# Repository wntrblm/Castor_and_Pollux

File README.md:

# Winterbloom Castor & Pollux

Castor & Pollux is a Roland Juno-inspired oscillator in Eurorack format.

More details available at https://winterbloom.com/shop/winterbloom-castor-and-pollux

## Repository layout

This repository contains the hardware design files, firmware files, factory setup scripts, and user guide for Castor & Pollux.

- **factory/** contains the scripts used to program, test, and calibrate the module after assembly. These scripts are all written in Python.
- **firmware/** contains the firmware source code, build scripts, and third-party dependencies. The firmware is written in C using GCC ARM.
- **hardware/** contains the hardware design files for the mainboard, jackboard, panel, and programming board. These are all created using KiCAD.
- **user_guide/** contains the user's guide source files. These are written in Markdown and published using MkDocs.

## License and contributing

Castor & Pollux is open-source hardware and software, however, licensing a project like this is a little complicated. Please take a chance to review the [LICENSE](LICENSE.md) file.

We welcome contributions! Please read our [Contributing Guide](CONTRIBUTING.md) and [Code of Conduct](CODE_OF_CONDUCT.md).

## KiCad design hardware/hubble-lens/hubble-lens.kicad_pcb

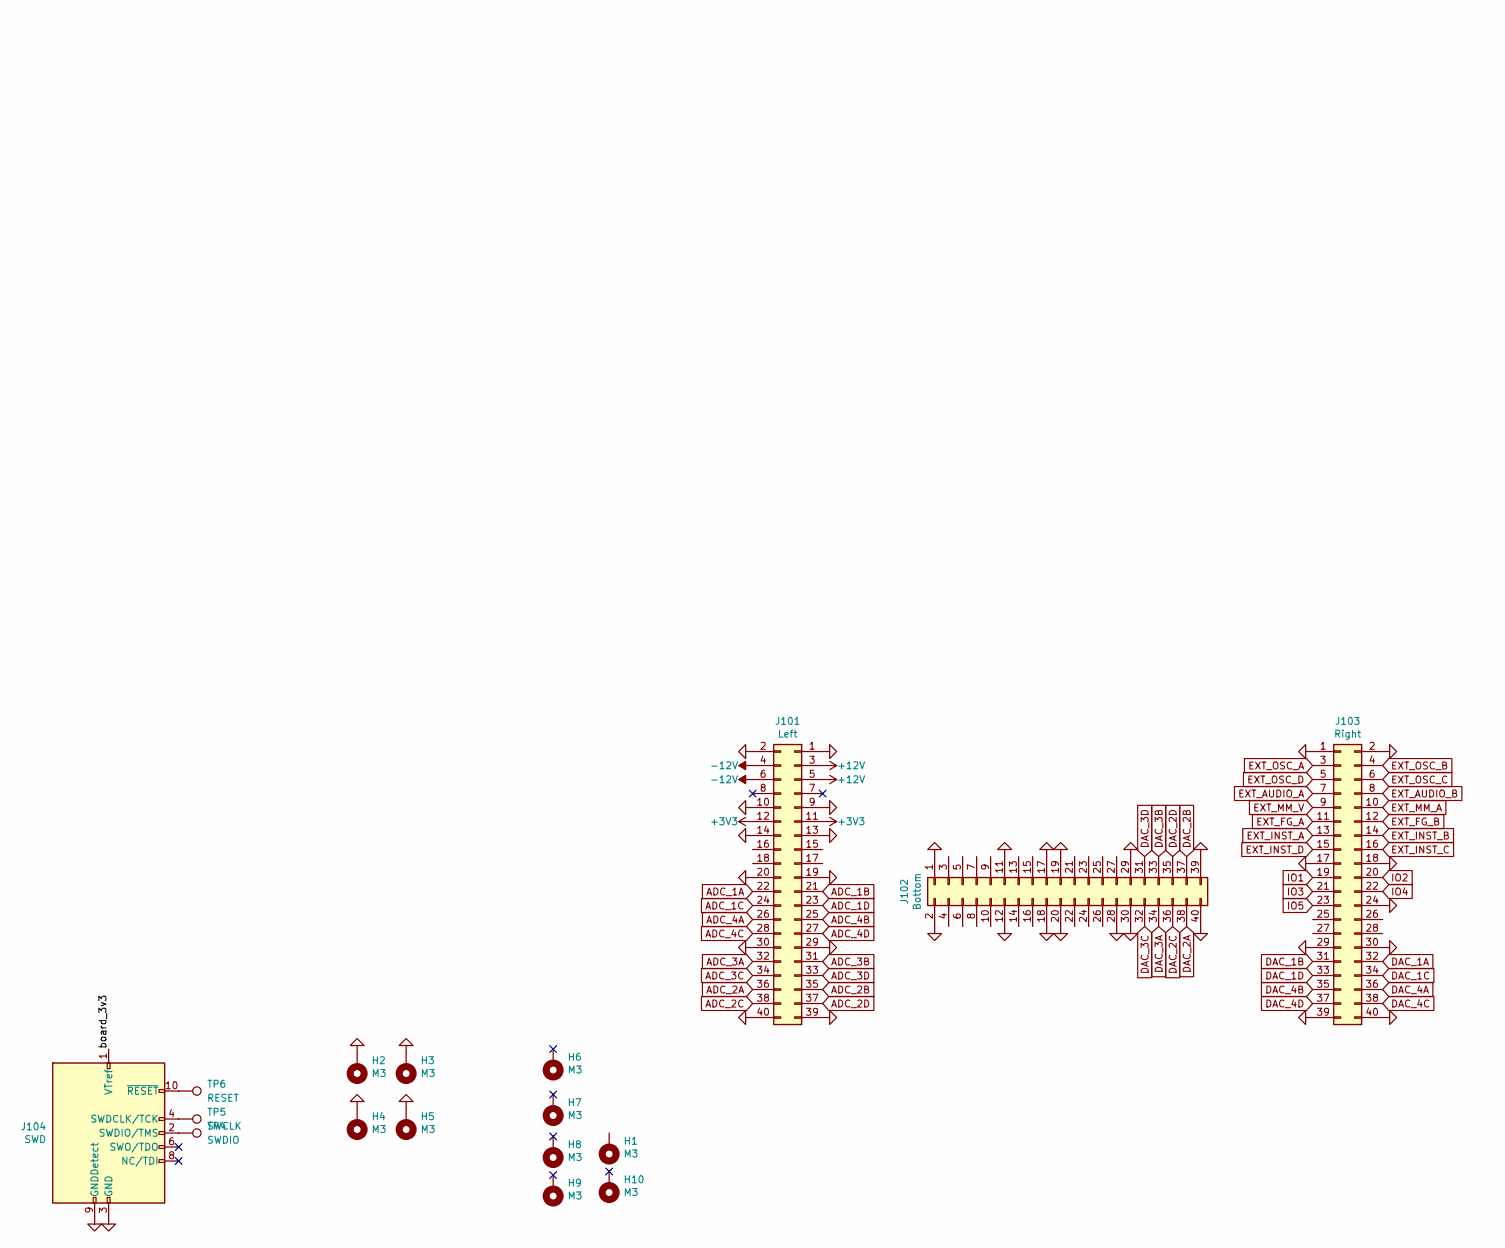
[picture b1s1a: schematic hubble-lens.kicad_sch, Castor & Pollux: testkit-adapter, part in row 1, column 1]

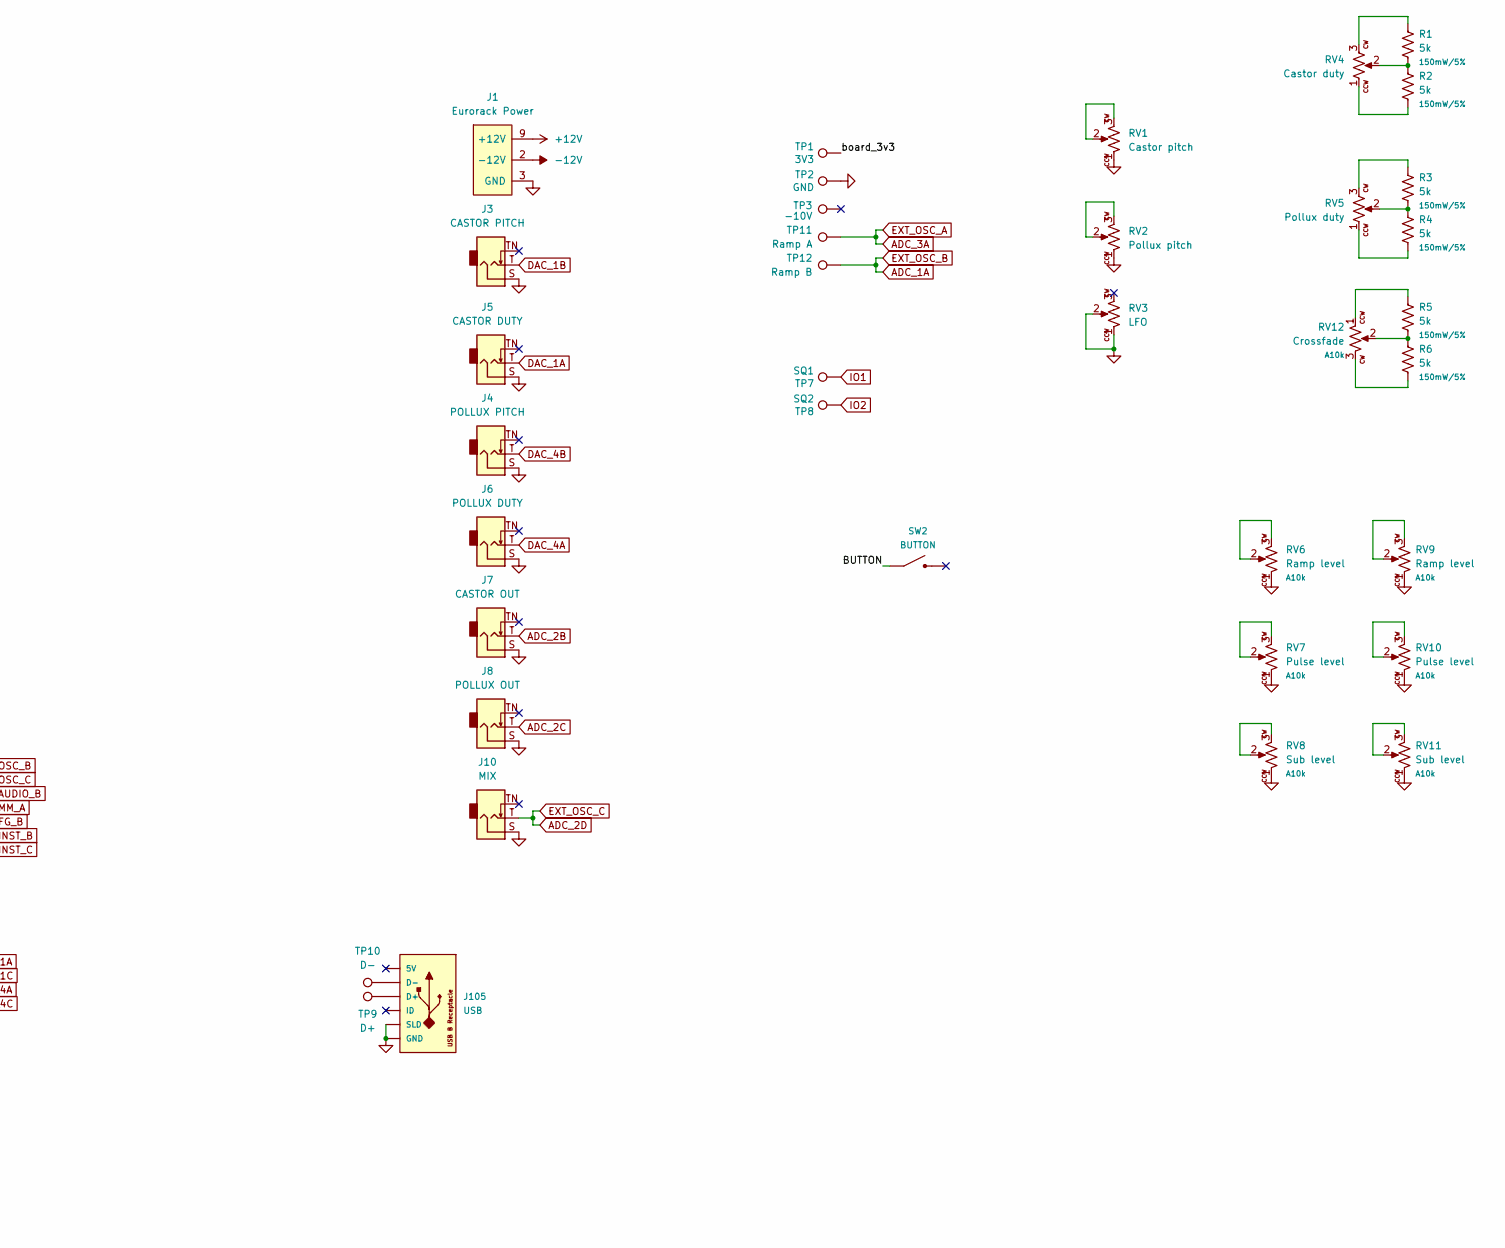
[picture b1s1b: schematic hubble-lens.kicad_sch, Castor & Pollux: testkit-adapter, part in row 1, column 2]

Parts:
H1, H6, H7, H8, H9, H10: M3; MountingHole_3.2mm_M3
H2, H3, H4, H5: M3; MountingHole_3.2mm_M3_Pad_Via
J1: Eurorack Power; Eurorack_Power_2x5_Shrouded; MPN 4UCONN 20253, On-shore 302-S101
J3: CASTOR PITCH; AudioJack_WQP518MA; MPN WQP-WQP518MA
J4: POLLUX PITCH; AudioJack_WQP518MA; MPN WQP-WQP518MA
J5: CASTOR DUTY; AudioJack_WQP518MA; MPN WQP-WQP518MA
J6: POLLUX DUTY; AudioJack_WQP518MA; MPN WQP-WQP518MA
J7: CASTOR OUT; AudioJack_WQP518MA; MPN WQP-WQP518MA
J8: POLLUX OUT; AudioJack_WQP518MA; MPN WQP-WQP518MA
J10: MIX; AudioJack_WQP518MA; MPN WQP-WQP518MA
J101: Left; PinSocket_2x20_P2.54mm_Vertical
J102: Bottom; PinSocket_2x20_P2.54mm_Vertical
J103: Right; PinSocket_2x20_P2.54mm_Vertical
J104: SWD; PinHeader_2x05_P1.27mm_Vertical
J105: USB; USB_B_Micro_Receptacle
R1, R2, R3, R4, R5, R6: 5k; R_0603_HandSolder; Rating 150mW/5%
RV1: Castor pitch; Potentiometer_Alpha_R0904N; Rating A10k
RV2: Pollux pitch; Potentiometer_Alpha_R0904N; Rating A10k
RV3: LFO; Potentiometer_Alpha_R0904N; Rating A10k
RV4: Castor duty; Potentiometer_Alpha_R0904N; Rating A10k
RV5: Pollux duty; Potentiometer_Alpha_R0904N; Rating A10k
RV6, RV9: Ramp level; Potentiometer_Alpha_R0904N; Rating A10k; MPN R0904N-B10K L-25KQ/LWS
RV7, RV10: Pulse level; Potentiometer_Alpha_R0904N; Rating A10k; MPN R0904N-B10K L-25KQ/LWS
RV8, RV11: Sub level; Potentiometer_Alpha_R0904N; Rating A10k; MPN R0904N-B10K L-25KQ/LWS
RV12: Crossfade; Potentiometer_Alpha_R0904N; Rating A10k
SW2: BUTTON; Tactile_Switch_6mm; MPN TL1105SPF160Q, TL1105SPF100Q, TL1105SPF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
TP1: 3V3; TestPoint_THTPad_D2.0mm_Drill1.0mm
TP2: GND; TestPoint_THTPad_D2.0mm_Drill1.0mm
TP3: -10V; TestPoint_THTPad_D2.0mm_Drill1.0mm
TP4: SWDIO; TestPoint_THTPad_D2.0mm_Drill1.0mm
TP5: SWCLK; TestPoint_THTPad_D2.0mm_Drill1.0mm
TP6: RESET; TestPoint_THTPad_D2.0mm_Drill1.0mm
TP7: SQ1; TestPoint_THTPad_D2.0mm_Drill1.0mm
TP8: SQ2; TestPoint_THTPad_D2.0mm_Drill1.0mm
TP9: D+; TestPoint_THTPad_D2.0mm_Drill1.0mm
TP10: D-; TestPoint_THTPad_D2.0mm_Drill1.0mm
TP11: Ramp A; TestPoint_THTPad_D2.0mm_Drill1.0mm
TP12: Ramp B; TestPoint_THTPad_D2.0mm_Drill1.0mm

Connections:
+3V3: J101.11, J101.12
+12V: J1.9 (+12V), J1.10 (+12V), J101.3, J101.5
-12V: J1.1 (-12V), J1.2 (-12V), J101.4, J101.6
/BUTTON: SW2.1
/board_3v3: J104.1 (VTref), TP1.1
ADC_1A: J101.22, J103.4, TP12.1
ADC_1B: J101.21
ADC_1C: J101.24
ADC_1D: J101.23
ADC_2A: J101.36
ADC_2B: J7.T (Tip), J101.35
ADC_2C: J8.T (Tip), J101.38
ADC_2D: J10.T (Tip), J101.37, J103.6
ADC_3A: J101.32, J103.3, TP11.1
ADC_3B: J101.31
ADC_3C: J101.34
ADC_3D: J101.33
ADC_4A: J101.26
ADC_4B: J101.25
ADC_4C: J101.28
ADC_4D: J101.27
DAC_1A: J5.T (Tip), J103.32
DAC_1B: J3.T (Tip), J103.31
DAC_1C: J103.34
DAC_1D: J103.33
DAC_2A: J102.38
DAC_2B: J102.37
DAC_2C: J102.36
DAC_2D: J102.35
DAC_3A: J102.34
DAC_3B: J102.33
DAC_3C: J102.32
DAC_3D: J102.31
DAC_4A: J6.T (Tip), J103.36
DAC_4B: J4.T (Tip), J103.35
DAC_4C: J103.38
DAC_4D: J103.37
EXT_AUDIO_A: J103.7
EXT_AUDIO_B: J103.8
EXT_FG_A: J103.11
EXT_FG_B: J103.12
EXT_INST_A: J103.13
EXT_INST_B: J103.14
EXT_INST_C: J103.16
EXT_INST_D: J103.15
EXT_MM_A: J103.10
EXT_MM_V: J103.9
EXT_OSC_D: J103.5
GND: H2.1, H3.1, H4.1, H5.1, J1.3 (GND), J1.4 (GND), J1.5 (GND), J1.6 (GND), J1.7 (GND), J1.8 (GND), J3.S (Sleeve), J4.S (Sleeve), J5.S (Sleeve), J6.S (Sleeve), J7.S (Sleeve), J8.S (Sleeve), J10.S (Sleeve), J101.1, J101.2, J101.9, J101.10, J101.13, J101.14, J101.19, J101.20, J101.29, J101.30, J101.39, J101.40, J102.1, J102.2, J102.11, J102.12, J102.17, J102.18, J102.19, J102.20, J102.28, J102.29, J102.30, J102.39, J102.40, J103.1, J103.2, J103.17, J103.18, J103.24, J103.29, J103.30, J103.39, J103.40, J104.3 (GND), J104.5 (GND), J104.9 (GNDDetect), J105.5 (GND), J105.S1 (SLD), J105.S2 (SLD), J105.S3 (SLD), J105.S4 (SLD), J105.S5 (SLD), J105.S6 (SLD), RV1.1, RV2.1, RV3.1, RV3.2, RV6.1, RV7.1, RV8.1, RV9.1, RV10.1, RV11.1, TP2.1
IO1: J103.19, TP7.1
IO2: J103.20, TP8.1
IO3: J103.21
IO4: J103.22
IO5: J103.23
unnamed: J104.2 (SWDIO/TMS), TP4.1
unnamed: J104.4 (SWDCLK/TCK), TP5.1
unnamed: J104.10 (~RESET), TP6.1
unnamed: RV1.2, RV1.3
unnamed: RV2.2, RV2.3
unnamed: R2.1, RV4.1
unnamed: R1.1, R2.2, RV4.2
unnamed: R1.2, RV4.3
unnamed: R4.1, RV5.1
unnamed: R3.1, R4.2, RV5.2
unnamed: R3.2, RV5.3
unnamed: RV6.2, RV6.3
unnamed: RV7.2, RV7.3
unnamed: RV8.2, RV8.3
unnamed: RV9.2, RV9.3
unnamed: RV10.2, RV10.3
unnamed: RV11.2, RV11.3
unnamed: R5.2, RV12.1
unnamed: R5.1, R6.2, RV12.2
unnamed: R6.1, RV12.3
unnamed: J105.3 (D+), TP9.1
unnamed: J105.2 (D-), TP10.1

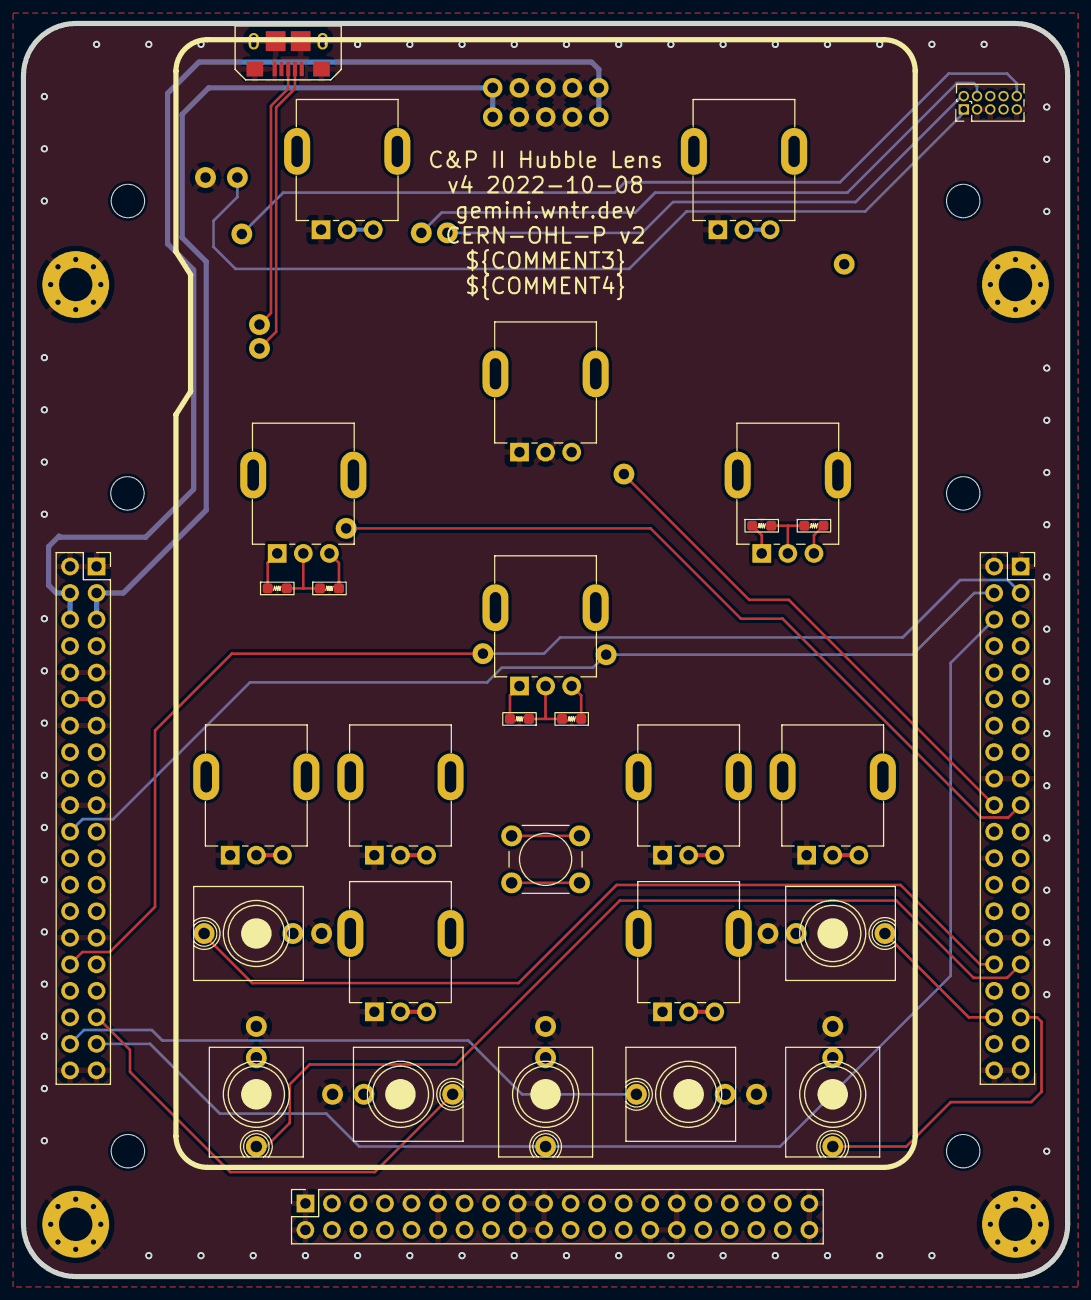
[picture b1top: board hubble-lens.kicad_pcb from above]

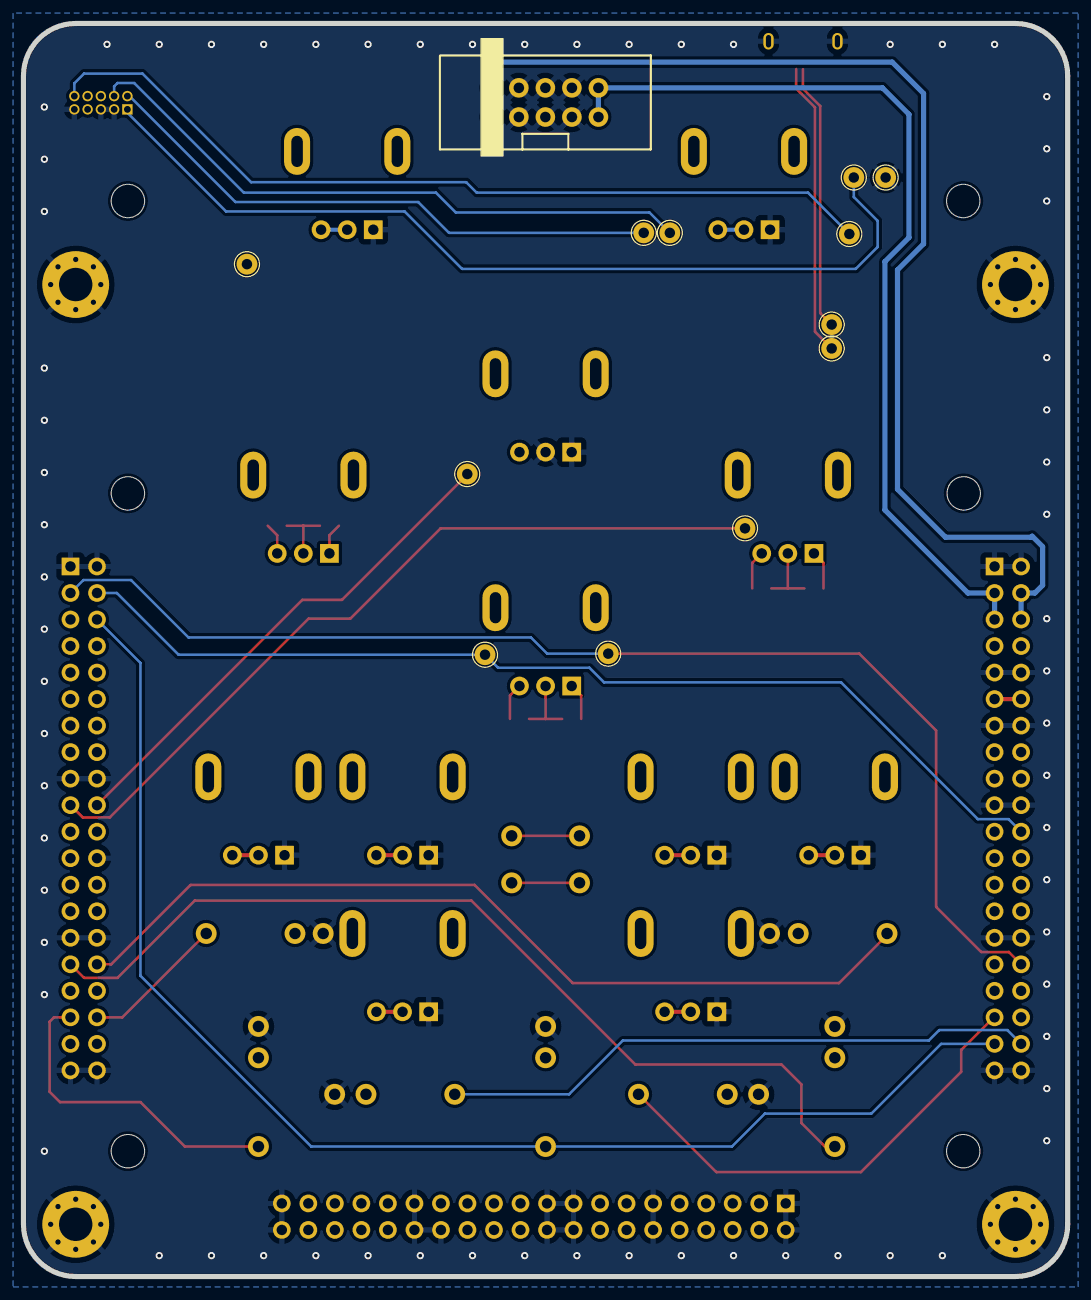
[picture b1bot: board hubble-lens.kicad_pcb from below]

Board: 2 copper layers, 100.0 x 120.0 mm, 54 parts (13 on the bottom side), 38 nets.

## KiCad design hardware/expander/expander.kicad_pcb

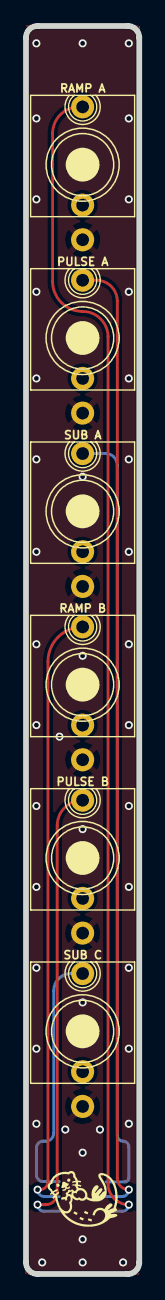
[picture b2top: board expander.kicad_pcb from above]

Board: 2 copper layers, 9.8 x 108.0 mm, 7 parts (1 on the bottom side), 7 nets.

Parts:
J1: EXT; Connector_Cortex_Debug_IDC_2x05_P1.27mm_Vertical_Shrouded_S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
J2: RAMP A; AudioJack_WQP518MA
J3: PULSE A; AudioJack_WQP518MA
J4: SUB A; AudioJack_WQP518MA
J5: RAMP B; AudioJack_WQP518MA
J6: PULSE B; AudioJack_WQP518MA
J7: SUB C; AudioJack_WQP518MA

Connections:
/CASTOR_PULSE_IN: J1.6, J3.T (Tip)
/CASTOR_RAMP_IN: J1.4, J2.T (Tip)
/CASTOR_SUB_IN: J1.8, J4.T (Tip)
/POLLUX_PULSE_IN: J1.3, J6.T (Tip)
/POLLUX_RAMP_IN: J1.5, J5.T (Tip)
/POLLUX_SUB_IN: J1.7, J7.T (Tip)
GND: J1.1, J1.2, J1.9, J1.10, J2.S (Sleeve), J3.S (Sleeve), J4.S (Sleeve), J5.S (Sleeve), J6.S (Sleeve), J7.S (Sleeve)

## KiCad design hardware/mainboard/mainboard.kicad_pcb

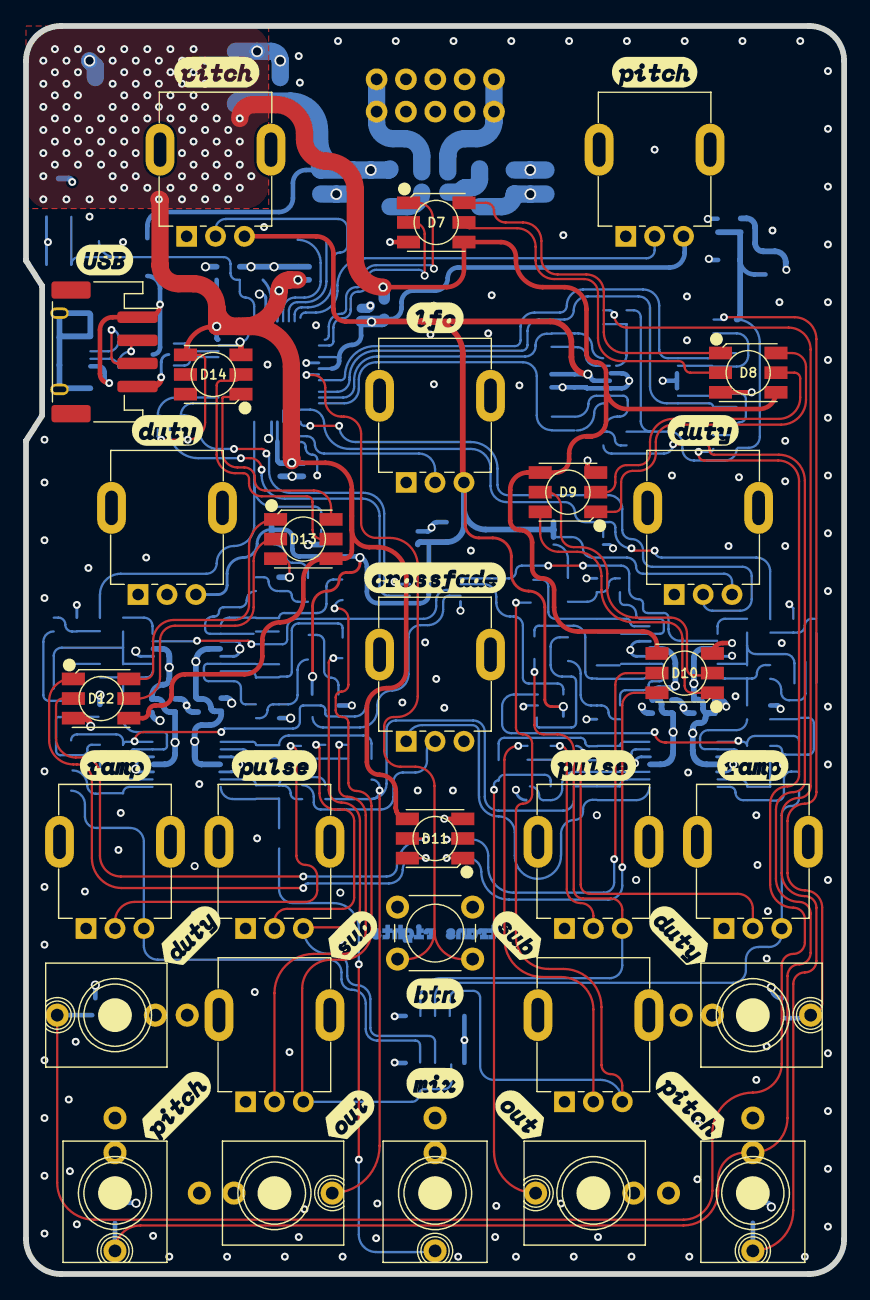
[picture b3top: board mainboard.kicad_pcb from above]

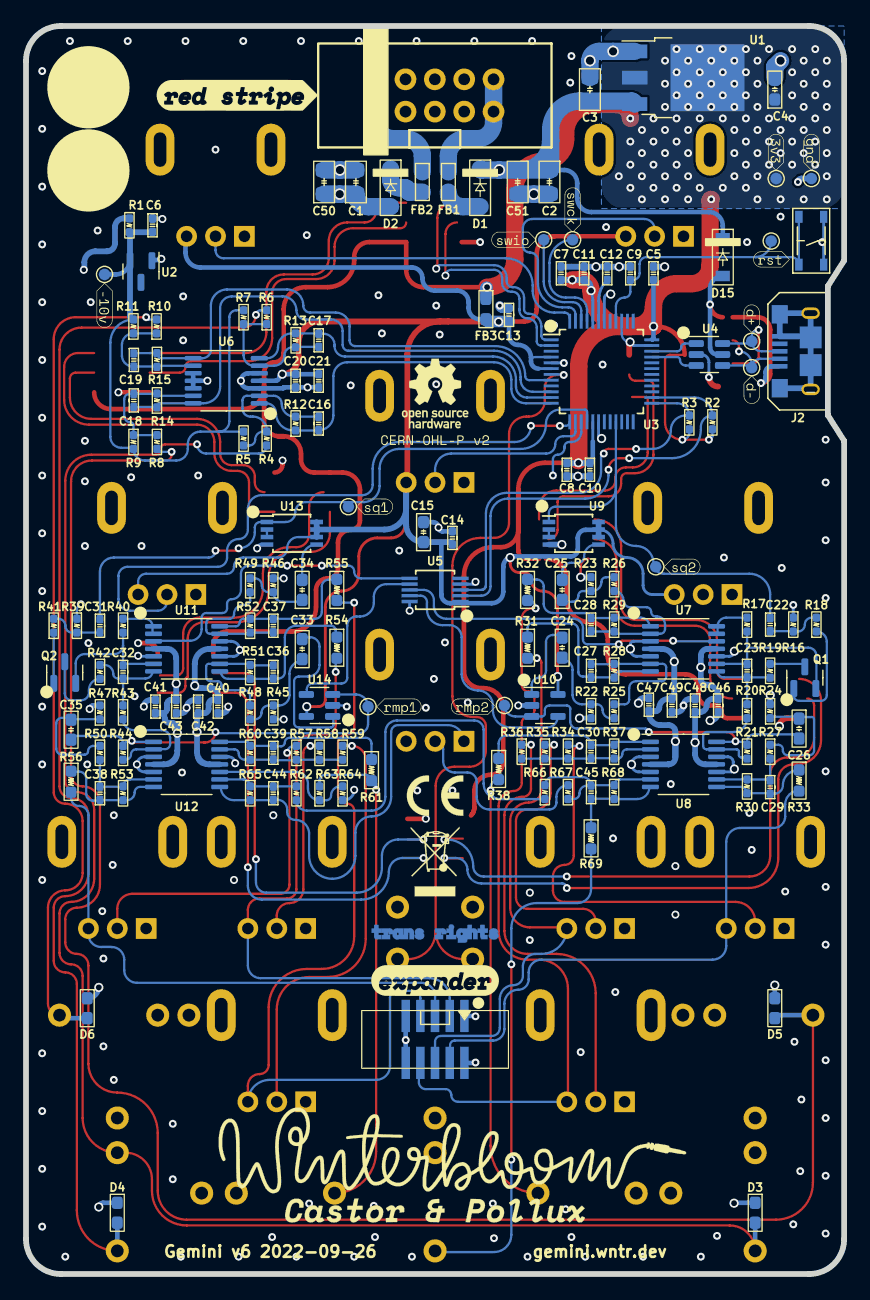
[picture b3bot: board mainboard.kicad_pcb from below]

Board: 4 copper layers, 70.8 x 108.0 mm, 191 parts (162 on the bottom side), 126 nets.

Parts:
C1, C2, C3, C50, C51: 22u; C_0805_HandSolder
C4, C15, C24, C25, C26, C33, C34, C35: 10u; C_0603_HandSolder
C5, C6, C8, C9, C10, C11, C13, C14, C20, C40, C41, C42, C43, C46, C47, C48, C49: 100n; C_0402_HandSolder
C7, C12, C21: 1u; C_0402_HandSolder
C16, C17, C18, C19: 2n2; C_0402_HandSolder
C22, C31: 270p; C_0402_HandSolder
C23, C32: 1n; C_0402_HandSolder
C27, C28, C29, C30, C36, C37, C38, C39, C44, C45: 18p; C_0402_HandSolder
D1, D2, D15: 30V; D_SOD-123
D3, D4, D5, D6: ESD; C_0603_HandSolder
D7, D8, D9, D10, D11, D12, D13, D14: Dotstar; LED_APA102_Dotstar_5050
FB1, FB2, FB3: 600R@100MHz; L_0603_HandSolder
J1: Eurorack Power; Eurorack_Power_2x5_Shrouded
J2: USB; USB_B_Micro_Receptacle
J3: CASTOR PITCH; AudioJack_WQP518MA
J4: POLLUX PITCH; AudioJack_WQP518MA
J5: CASTOR DUTY; AudioJack_WQP518MA
J6: POLLUX DUTY; AudioJack_WQP518MA
J7, J8: OSC OUT; AudioJack_WQP518MA
J9: EXT; Connector_Cortex_Debug_IDC_2x05_P1.27mm_Vertical_Shrouded_S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
J10: MIX; AudioJack_WQP518MA
J11: USB ALT; JST_PH_S4B-PH-SM4-TB_1x04-1MP_P2.00mm_Horizontal
Q1, Q2: MMBT3906; SOT-23
R1: 2k2; R_0402_HandSolder
R2, R3: 4k7; R_0402_HandSolder
R4, R6, R8, R10, R22, R23, R24, R34, R35, R36, R37, R45, R46, R47, R57, R58, R59, R60, R62, R63, R64, R65, R66, R67, R68: 100k; R_0402_HandSolder
R5, R7: 162k; R_0402_HandSolder
R9, R11: 196k; R_0402_HandSolder
R12, R13: 48k7; R_0402_HandSolder
R14, R15: 61k9; R_0402_HandSolder
R16, R21, R25, R26, R27, R39, R44, R48, R49, R50: 10k; R_0402_HandSolder
R17, R40: 200k; R_0402_HandSolder
R18, R41: 1k; R_0402_HandSolder
R19, R42: 270R; R_0402_HandSolder
R20, R28, R29, R30, R43, R51, R52, R53: 33k; R_0402_HandSolder
R31, R32, R33, R38, R54, R55, R56, R61, R69: 1k; R_0603_HandSolder
RV1: Castor pitch; Potentiometer_Alpha_R0904N
RV2: Pollux pitch; Potentiometer_Alpha_R0904N
RV3: LFO; Potentiometer_Alpha_R0904N
RV4: Castor duty; Potentiometer_Alpha_R0904N
RV5: Pollux duty; Potentiometer_Alpha_R0904N
RV6, RV9: Ramp level; Potentiometer_Alpha_R0904N
RV7, RV10: Pulse level; Potentiometer_Alpha_R0904N
RV8, RV11: Sub level; Potentiometer_Alpha_R0904N
RV12: Crossfade; Potentiometer_Alpha_R0904N
SW1: RESET; Tactile_Switch_4.2mm
SW2: BUTTON; Tactile_Switch_6mm
TP1: 3V3; TestPoint_Pad_D1.0mm
TP2: GND; TestPoint_Pad_D1.0mm
TP3: -10V; TestPoint_Pad_D1.0mm
TP4: SWDIO; TestPoint_Pad_D1.0mm
TP5: SWCLK; TestPoint_Pad_D1.0mm
TP6: RESET; TestPoint_Pad_D1.0mm
TP7: SQ2; TestPoint_Pad_D1.0mm
TP8: SQ1; TestPoint_Pad_D1.0mm
TP9: D+; TestPoint_Pad_D1.0mm
TP10: D-; TestPoint_Pad_D1.0mm
TP11, TP12: Ramp; TestPoint_Pad_D1.0mm
U1: LD1117-3.3; TO-252-3_TabPin2
U2: LM4040DBZ-10; SOT-23
U3: ATSAMD21G18A-A; TQFP-48_7x7mm_P0.5mm
U4: USBLC6-2SC6; SOT-23-6
U5: MCP4728; MSOP-10_3x3mm_P0.5mm
U6: MCP6004; TSSOP-14_4.4x5mm_P0.65mm
U7, U8, U11, U12: TL074; TSSOP-14_4.4x5mm_P0.65mm
U9, U13: 74LVC2G74; TSSOP-8_3x3mm_P0.65mm
U10, U14: MCP6001-OT; SOT-23-5

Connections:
+3.3V: C4.1, C5.1, C7.1, C8.1, C10.1, C11.1, D7.4 (VCC), D8.4 (VCC), D9.4 (VCC), D10.4 (VCC), D11.4 (VCC), D12.4 (VCC), D13.4 (VCC), D14.4 (VCC), FB3.1, R2.1, R3.1, TP1.1, U1.2 (VO), U3.17 (VDDIO), U3.36 (VDDIO), U3.44 (VDDIN)
+3.3VA: C13.1, C14.1, C15.1, C20.2, C21.2, FB3.2, RV1.3, RV2.3, RV3.3, RV4.3, RV5.3, U3.4 (PA03), U3.6 (VDDANA), U5.1 (VDD), U6.4 (V+), U9.6 (~CLR), U9.7 (~PRE), U9.8 (VCC), U10.5 (V+), U13.6 (~CLR), U13.7 (~PRE), U13.8 (VCC), U14.5 (V+)
+12V: C2.1, C3.1, C41.1, C43.1, C47.1, C49.1, C51.1, D1.1 (K), D15.1 (K), U1.3 (VI), U7.4 (V+), U8.4 (V+), U11.4 (V+), U12.4 (V+)
-12V: C1.1, C40.2, C42.2, C46.2, C48.2, C50.1, D2.2 (A), R1.1, U7.11 (V-), U8.11 (V-), U11.11 (V-), U12.11 (V-)
/Analog inputs/CASTOR_DUTY_CV: C18.2, R14.1, U3.10 (PA05), U6.14
/Analog inputs/CASTOR_PITCH_CV: C16.2, R12.1, U3.12 (PA07), U6.1
/Analog inputs/CV A IN: D3.2 (A2), J3.T (Tip), J4.TN (Tip_normalize), R4.2
/Analog inputs/CV B IN: D4.2 (A2), J4.T (Tip), R6.2
/Analog inputs/DUTY A IN: D5.2 (A2), J5.T (Tip), R8.2
/Analog inputs/DUTY B IN: D6.2 (A2), J6.T (Tip), R10.2
/Analog inputs/POLLUX_DUTY_CV: C19.2, R15.1, U3.8 (PB09), U6.8
/Analog inputs/POLLUX_PITCH_CV: C17.2, R13.1, U3.11 (PA06), U6.7
/Castor/CHARGE_CV_IN: U5.8 (VOUTC), U7.12 (+)
/Castor/MIX_OUT: J7.T (Tip), R38.2, R62.2, R66.1
/Castor/PULSE_OUT: J9.6, R31.2, RV7.3
/Castor/PWM_CV_IN: U5.9 (VOUTD), U10.4 (-)
/Castor/RAMP_OUT: J9.4, R33.2, RV6.3
/Castor/SQUARE_IN: C22.2, TP7.1, U3.21 (PA12), U9.1 (C)
/Castor/SUB_OUT: J9.8, R32.2, RV8.3
/Castor/pulse_pre: C24.2, U10.1
/Castor/ramp_pre: C26.2, R21.2, TP11.1, U8.14, U10.3 (+)
/Castor/sub_pre: C25.2, U9.5 (Q)
/LEDs/CLK: D7.2 (CI), U3.2 (PA01)
/LEDs/DATA: D7.1 (DI), U3.1 (PA00)
/MCU/BUTTON: SW2.1, U3.7 (PB08)
/MCU/CASTOR_DUTY_POT: RV4.2, U3.15 (PA10)
/MCU/CASTOR_PITCH_POT: RV1.2, U3.47 (PB02)
/MCU/CONN_D+: J2.3 (D+), J11.3, TP9.1, U4.6 (I/O1)
/MCU/CONN_D-: J2.2 (D-), J11.2, TP10.1, U4.4 (I/O2)
/MCU/D+: U3.34 (PA25), U4.1 (I/O1)
/MCU/D-: U3.33 (PA24), U4.3 (I/O2)
/MCU/I2C_SCL: R2.2, U3.26 (PA17), U5.2 (SCL)
/MCU/I2C_SDA: R3.2, U3.25 (PA16), U5.3 (SDA)
/MCU/LFO_POT: RV3.2, U3.14 (PA09)
/MCU/POLLUX_CHARGE_CV: U5.6 (VOUTA), U11.3 (+)
/MCU/POLLUX_DUTY_POT: RV5.2, U3.13 (PA08)
/MCU/POLLUX_PITCH_POT: RV2.2, U3.48 (PB03)
/MCU/POLLUX_PWM_CV: U5.7 (VOUTB), U14.4 (-)
/MCU/POLLUX_SQUARE_OUT: C31.2, TP8.1, U3.16 (PA11), U13.1 (C)
/MCU/RESET: C9.1, SW1.1, TP6.1, U3.40 (~RESET)
/MCU/SWCLK: TP5.1, U3.45 (PA30)
/MCU/SWDIO: TP4.1, U3.46 (PA31)
/MCU/VDDCORE: C12.2, U3.43 (VDDCORE)
/Mixer & outputs/POLLUX_MIX_IN: J8.T (Tip), R61.2, R63.2
/Mixer & outputs/POLLUX_PULSE_IN: J9.3, R54.2, RV10.3
/Mixer & outputs/POLLUX_RAMP_IN: J9.5, R56.2, RV9.3
/Mixer & outputs/POLLUX_SUB_IN: J9.7, R55.2, RV11.3
/Pollux/pulse_pre: C33.2, U14.1
/Pollux/ramp_pre: C35.2, R44.2, TP12.1, U12.1, U14.3 (+)
/Pollux/sub_pre: C34.2, U13.5 (Q)
GND: C1.2, C2.2, C3.2, C4.2, C5.2, C6.2, C7.2, C8.2, C9.2, C10.2, C11.2, C12.1, C13.2, C14.2, C15.2, C20.1, C21.1, C40.1, C41.2, C42.1, C43.2, C46.1, C47.2, C48.1, C49.2, C50.2, C51.2, D3.1 (A1), D4.1 (A1), D5.1 (A1), D6.1 (A1), D7.3 (GND), D8.3 (GND), D9.3 (GND), D10.3 (GND), D11.3 (GND), D12.3 (GND), D13.3 (GND), D14.3 (GND), J1.3 (GND), J1.4 (GND), J1.5 (GND), J1.6 (GND), J1.7 (GND), J1.8 (GND), J2.5 (GND), J2.S1 (SLD), J2.S2 (SLD), J2.S3 (SLD), J2.S4 (SLD), J2.S5 (SLD), J2.S6 (SLD), J3.S (Sleeve), J3.TN (Tip_normalize), J4.S (Sleeve), J5.S (Sleeve), J5.TN (Tip_normalize), J6.S (Sleeve), J6.TN (Tip_normalize), J7.S (Sleeve), J8.S (Sleeve), J9.1, J9.2, J9.9, J9.10, J10.S (Sleeve), J11.4, R16.1, R22.2, R23.2, R24.2, R39.1, R45.2, R46.2, R47.2, R64.1, RV1.1, RV2.1, RV3.1, RV4.1, RV5.1, RV6.1, RV7.1, RV8.1, RV9.1, RV10.1, RV11.1, RV12.3, SW1.2, SW2.2, TP2.1, U1.1 (GND), U2.1 (K), U3.5 (GNDANA), U3.18 (GND), U3.35 (GND), U3.39 (PA27), U3.42 (GND), U4.2 (GND), U5.4 (~LDAC), U5.10 (VSS), U6.3 (+), U6.5 (+), U6.10 (+), U6.11 (V-), U6.12 (+), U7.3 (+), U7.5 (+), U7.10 (+), U8.3 (+), U8.5 (+), U8.10 (+), U8.12 (+), U9.4 (GND), U10.2 (V-), U11.5 (+), U11.10 (+), U11.12 (+), U12.3 (+), U12.5 (+), U12.12 (+), U13.4 (GND), U14.2 (V-)
unnamed: C16.1, R4.1, R5.1, R12.2, U6.2 (-)
unnamed: C17.1, R6.1, R7.1, R13.2, U6.6 (-)
unnamed: C18.1, R8.1, R9.1, R14.2, U6.13 (-)
unnamed: C19.1, R10.1, R11.1, R15.2, U6.9 (-)
unnamed: C22.1, R16.2, R18.2
unnamed: C23.1, R19.1, R20.1, U7.8
unnamed: C23.2, Q1.2 (E), R17.2, U7.9 (-)
unnamed: C24.1, R22.1, R25.1
unnamed: C25.1, R23.1, R26.1
unnamed: C26.1, R24.1, R27.1
unnamed: C27.1, R28.2, R31.1, U7.7
unnamed: C27.2, R25.2, R28.1, U7.6 (-)
unnamed: C28.1, R29.2, R32.1, U7.1
unnamed: C28.2, R26.2, R29.1, U7.2 (-)
unnamed: C29.1, R30.2, R33.1, U8.8
unnamed: C29.2, R27.2, R30.1, U8.9 (-)
unnamed: C30.1, R37.2, R38.1, U8.1
unnamed: C30.2, R34.2, R35.2, R36.2, R37.1, U8.2 (-)
unnamed: C31.1, R39.2, R41.2
unnamed: C32.1, R42.1, R43.1, U11.7
unnamed: C32.2, Q2.2 (E), R40.2, U11.6 (-)
unnamed: C33.1, R45.1, R48.1
unnamed: C34.1, R46.1, R49.1
unnamed: C35.1, R47.1, R50.1
unnamed: C36.1, R51.2, R54.1, U11.8
unnamed: C36.2, R48.2, R51.1, U11.9 (-)
unnamed: C37.1, R52.2, R55.1, U11.14
unnamed: C37.2, R49.2, R52.1, U11.13 (-)
unnamed: C38.1, R53.2, R56.1, U12.7
unnamed: C38.2, R50.2, R53.1, U12.6 (-)
unnamed: C39.1, R60.2, R61.1, U12.14
unnamed: C39.2, R57.2, R58.2, R59.2, R60.1, U12.13 (-)
unnamed: C44.1, R65.2, RV12.1, U12.8
unnamed: C44.2, R62.1, R65.1, U12.9 (-)
unnamed: C45.1, R68.2, R69.1, U8.7
unnamed: C45.2, R66.2, R67.2, R68.1, U8.6 (-)
unnamed: D1.2 (A), FB1.2
unnamed: D2.1 (K), FB2.2
unnamed: D7.5 (CO), D8.2 (CI)
unnamed: D7.6 (DO), D8.1 (DI)
unnamed: D8.5 (CO), D9.2 (CI)
unnamed: D8.6 (DO), D9.1 (DI)
unnamed: D9.6 (DO), D10.1 (DI)
unnamed: D9.5 (CO), D10.2 (CI)
unnamed: D10.5 (CO), D11.2 (CI)
unnamed: D10.6 (DO), D11.1 (DI)
unnamed: D11.5 (CO), D12.2 (CI)
unnamed: D11.6 (DO), D12.1 (DI)
unnamed: D12.5 (CO), D13.2 (CI)
unnamed: D12.6 (DO), D13.1 (DI)
unnamed: D13.5 (CO), D14.2 (CI)
unnamed: D13.6 (DO), D14.1 (DI)
unnamed: FB1.1, J1.9 (+12V), J1.10 (+12V)
unnamed: FB2.1, J1.1 (-12V), J1.2 (-12V)
unnamed: J10.T (Tip), R69.2
unnamed: Q1.1 (B), R18.1
unnamed: Q1.3 (C), R19.2
unnamed: Q2.1 (B), R41.1
unnamed: Q2.3 (C), R42.2
unnamed: R17.1, U7.13 (-), U7.14
unnamed: R20.2, R21.1, U8.13 (-)
unnamed: R34.1, RV6.2
unnamed: R35.1, RV7.2
unnamed: R36.1, RV8.2
unnamed: R40.1, U11.1, U11.2 (-)
unnamed: R43.2, R44.1, U12.2 (-)
unnamed: R57.1, RV9.2
unnamed: R58.1, RV10.2
unnamed: R59.1, RV11.2
unnamed: R63.1, R64.2, U12.10 (+)
unnamed: R67.1, RV12.2
unnamed: U9.2 (D), U9.3 (~Q)
unnamed: U13.2 (D), U13.3 (~Q)
VREF-10: C6.1, R1.2, R5.2, R7.2, R9.2, R11.2, TP3.1, U2.2 (A)
VUSB: D15.2 (A), J2.1 (5V), J11.1, U4.5 (VBUS)

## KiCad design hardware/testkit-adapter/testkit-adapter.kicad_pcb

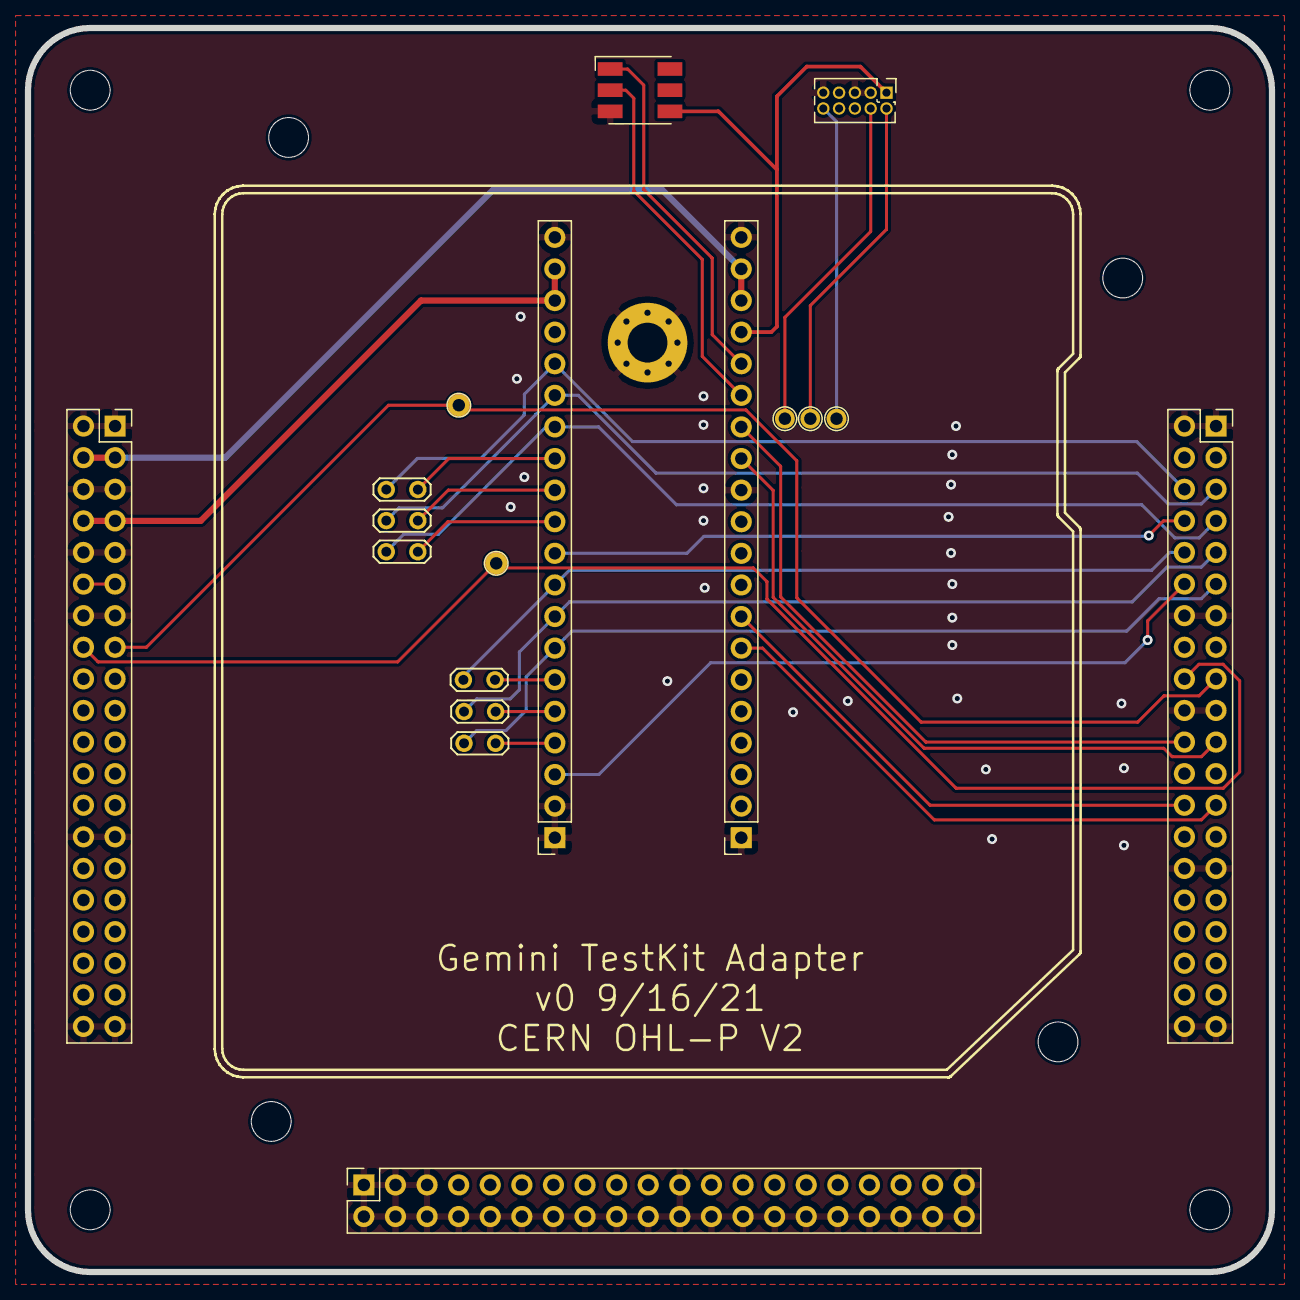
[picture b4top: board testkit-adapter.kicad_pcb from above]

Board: 2 copper layers, 100.0 x 100.0 mm, 27 parts (0 on the bottom side), 30 nets.

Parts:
D1: DOTSTAR; LED_RGB_5050-6
H1: M3; MountingHole_3.2mm_M3_Pad_Via
H2, H3, H4, H5, H6, H7, H8, H9: M3; MountingHole_3.2mm_M3
J1: LEFT; PinSocket_1x20_P2.54mm_Vertical
J2: RIGHT; PinSocket_1x20_P2.54mm_Vertical
J3: SWD; PinHeader_2x05_P1.27mm_Vertical
J4: Left; PinSocket_2x20_P2.54mm_Vertical
J5: Bottom; PinSocket_2x20_P2.54mm_Vertical
J6: Right; PinSocket_2x20_P2.54mm_Vertical
JP1: P Ramp Mix; TestPoint_2Pads_Pitch2.54mm_Drill0.8mm
JP2: P Pulse Mix; TestPoint_2Pads_Pitch2.54mm_Drill0.8mm
JP3: P Sub Mix; TestPoint_2Pads_Pitch2.54mm_Drill0.8mm
JP4: C Ramp Mix; TestPoint_2Pads_Pitch2.54mm_Drill0.8mm
JP5: C Pulse Mix; TestPoint_2Pads_Pitch2.54mm_Drill0.8mm
JP6: C Sub Mix; TestPoint_2Pads_Pitch2.54mm_Drill0.8mm
TP1: SWCLK; TestPoint_THTPad_D1.5mm_Drill0.7mm
TP2: SWDIO; TestPoint_THTPad_D1.5mm_Drill0.7mm
TP3: RESET; TestPoint_THTPad_D1.5mm_Drill0.7mm
TP4: CORE A; TestPoint_THTPad_D1.5mm_Drill0.7mm
TP5: CORE B; TestPoint_THTPad_D1.5mm_Drill0.7mm

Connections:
+3V3: J4.11, J4.12
+12V: J2.18, J2.19, J4.3, J4.4
-12V: J1.18, J1.19, J4.7, J4.8
/board_3v3: D1.4, J2.17, J3.1
/castor_pwm_mix_in: J1.5, JP5.2
/castor_ramp_mix_in: J1.6, JP4.2
/castor_sub_mix_in: J1.4, JP6.2
/dotstar_clk: D1.2, J2.15
/dotstar_data: D1.1, J2.16
/pollux_pwm_mix_in: J1.12, JP2.2
/pollux_ramp_mix_in: J1.13, JP1.2
/pollux_sub_mix_in: J1.11, JP3.2
A1*: J4.15, J6.17, TP4.1
A2*: J4.16, J6.18, TP5.1
AUDIO_IN_1A: J1.9, J6.10, JP4.1
AUDIO_IN_1B: J1.8, J6.9, JP5.1
AUDIO_IN_1C: J1.7, J6.11, JP6.1
AUDIO_IN_1D: J1.3, J6.12
AUDIO_IN_2A: J1.16, J6.6, JP1.1
AUDIO_IN_2B: J1.15, J6.5, JP2.1
AUDIO_IN_2C: J1.14, J6.7, JP3.1
AUDIO_IN_2D: J1.10, J6.8
DAC_1A: J2.8, J6.26
DAC_1B: J2.7, J6.25
DAC_2A: J2.14, J6.22
DAC_2B: J2.13, J6.21
GND: D1.3, H1.1, J1.1, J1.2, J1.20, J2.1, J2.12, J2.20, J3.3, J3.5, J3.9, J4.1, J4.2, J4.5, J4.6, J4.9, J4.10, J4.13, J4.14, J4.27, J4.28, J4.39, J4.40, J5.1, J5.2, J5.3, J5.4, J5.5, J5.6, J5.8, J5.10, J5.12, J5.14, J5.16, J5.18, J5.20, J5.21, J5.22, J5.24, J5.26, J5.28, J5.30, J5.32, J5.34, J5.36, J5.38, J5.39, J5.40, J6.1, J6.2, J6.13, J6.14, J6.19, J6.20, J6.29, J6.30, J6.39, J6.40
unnamed: J3.2, TP2.1
unnamed: J3.4, TP1.1
unnamed: J3.10, TP3.1

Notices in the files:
hardware/expander/expander.kicad_pcb:
CERN-OHL-P v2
